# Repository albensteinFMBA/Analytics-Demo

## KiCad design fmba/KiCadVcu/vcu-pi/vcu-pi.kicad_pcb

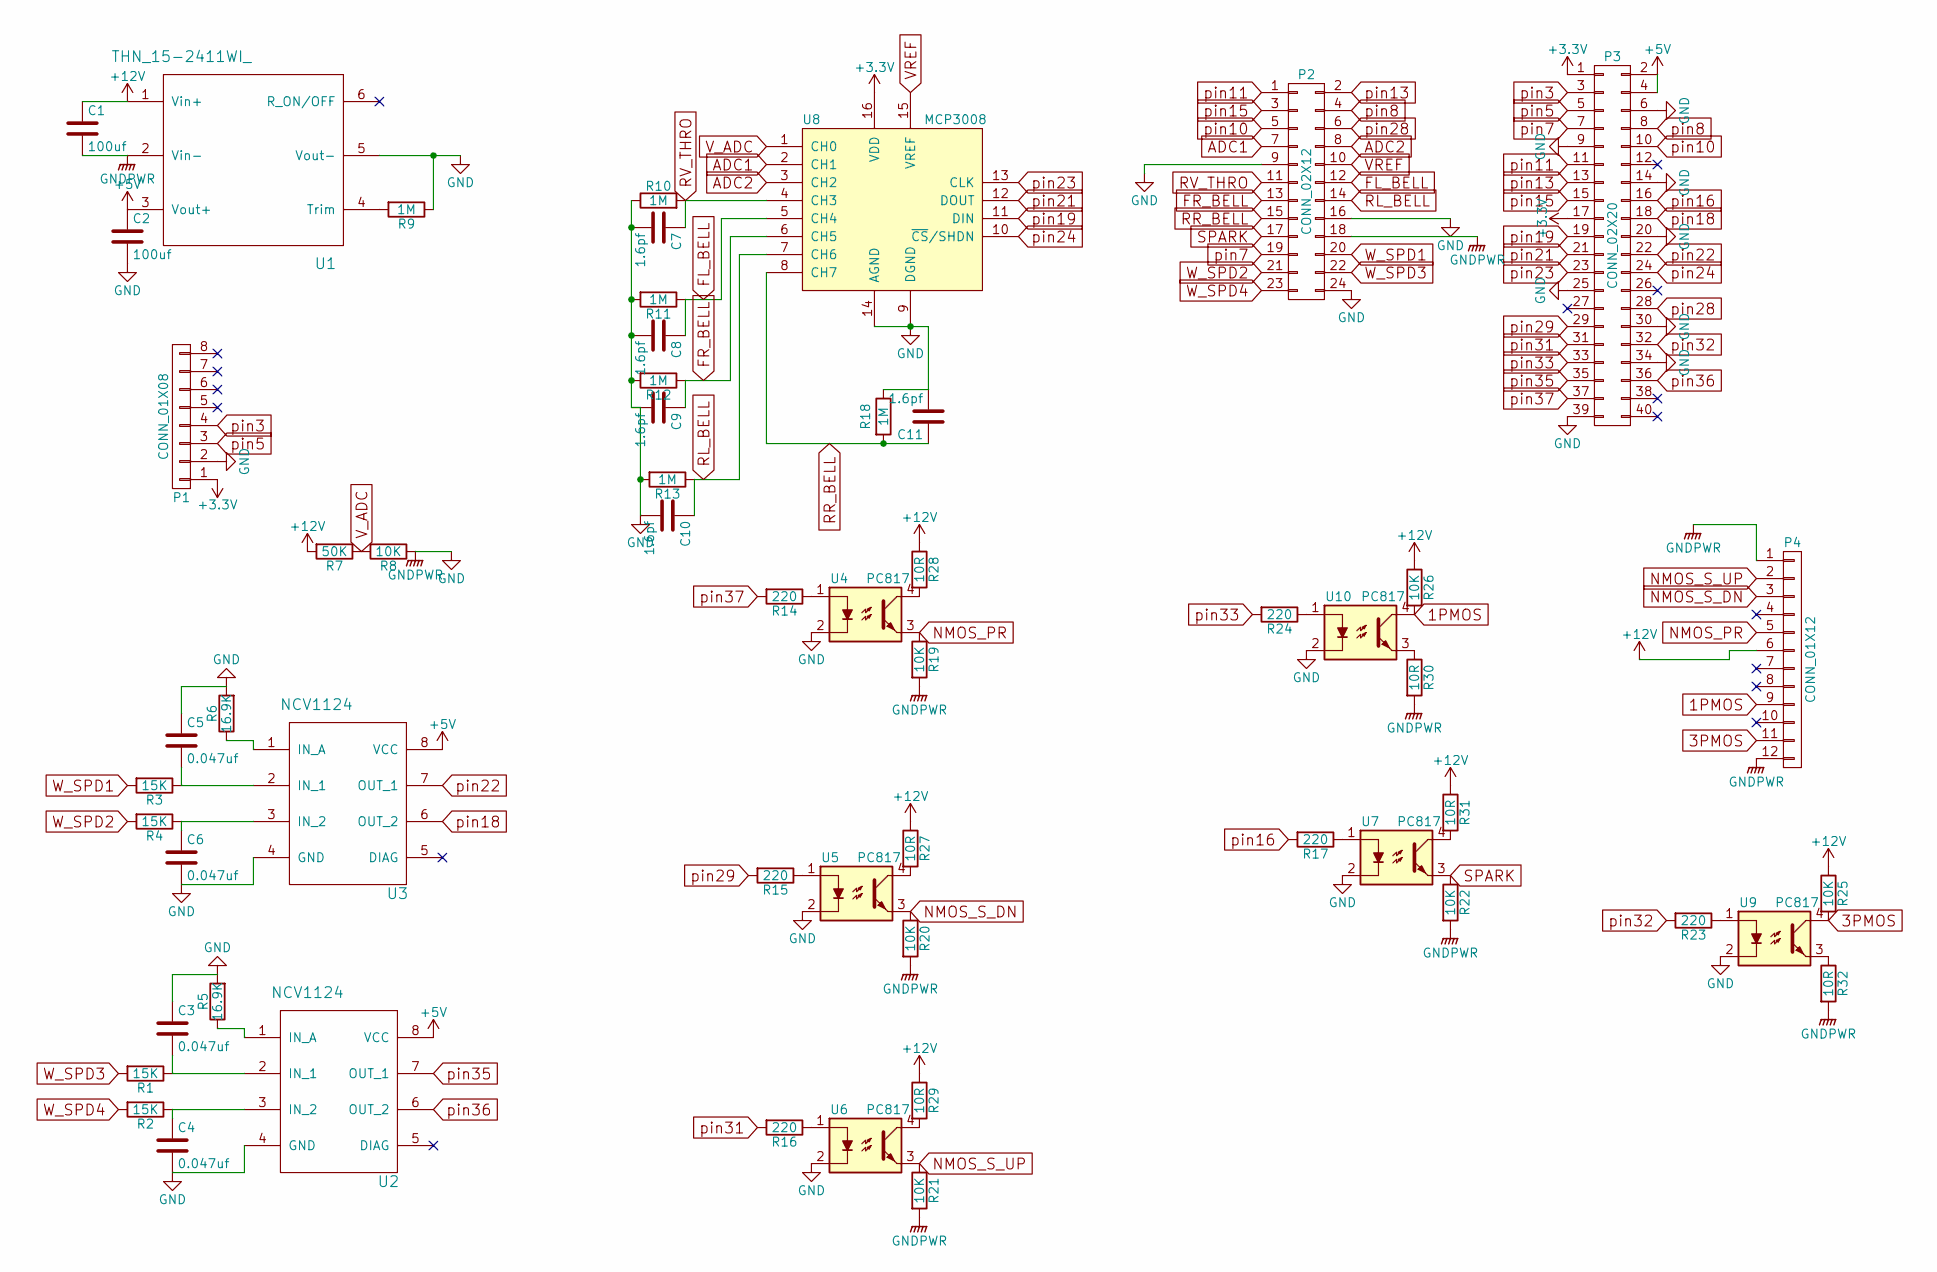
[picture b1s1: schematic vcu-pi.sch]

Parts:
C1, C2: 100uf; C_Radial_D10_L20_P5
C3, C4, C5, C6: 0.047uf; C_Rect_L13_W4_P10
C7, C8, C9, C10, C11: 1.6pf; C_Disc_D3_P2.5
P1: CONN_01X08; Socket_Strip_Straight_1x08
P2: CONN_02X12; connect24_2_12
P3: CONN_02X20; Socket_Strip_Straight_2x20
P4: CONN_01X12; connnector12-1
R1, R2, R3, R4: 15K; Resistor_Horizontal_RM20mm
R5, R6: 16.9K; Resistor_Horizontal_RM7mm
R7: 50K; Resistor_Horizontal_RM10mm
R8: 10K; Resistor_Horizontal_RM10mm
R9, R10, R11, R12, R13, R18: 1M; Resistor_Horizontal_RM10mm
R14, R15, R16, R17, R23, R24: 220; Resistor_Horizontal_RM7mm
R19, R20, R21, R22, R25, R26: 10K; Resistor_Horizontal_RM7mm
R27, R28, R29, R30, R31, R32: 10R; Resistor_Horizontal_RM7mm
U1: THN_15-2411WI_; THN_15-2411WI
U2, U3: NCV1124; SOIC-8_3.9x4.9mm_Pitch1.27mm
U4, U5, U6, U7, U9, U10: PC817; DIP-4_W7.62mm
U8: MCP3008; DIP-16_W7.62mm

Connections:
1PMOS: P4.9, R26.2, U10.4
3PMOS: P4.11, R25.2, U9.4
+3V3: P1.1, P3.1, P3.17, U8.16 (VDD)
+5V: C2.1, P3.2, P3.4, U1.3 (Vout+), U2.8 (VCC), U3.8 (VCC)
+12V: C1.1, P4.6, R7.2, R25.1, R26.1, R27.1, R28.1, R29.1, R31.1, U1.1 (Vin+)
ADC1: P2.7, U8.2 (CH1)
ADC2: P2.8, U8.3 (CH2)
FL_BELL: C8.1, P2.12, R11.1, U8.5 (CH4)
FR_BELL: C9.1, P2.13, R12.1, U8.6 (CH5)
GND: C1.2, C2.2, C3.1, C4.2, C5.1, C6.2, C7.2, C8.2, C9.2, C10.2, C11.2, P1.2, P2.9, P2.16, P2.18, P2.24, P3.6, P3.9, P3.14, P3.20, P3.25, P3.30, P3.34, P3.39, P4.1, P4.12, R5.2, R6.2, R8.1, R9.1, R10.1, R11.2, R12.2, R13.2, R18.1, R19.2, R20.2, R21.2, R22.2, R30.2, R32.2, U1.2 (Vin-), U1.5 (Vout-), U2.4 (GND), U3.4 (GND), U4.2, U5.2, U6.2, U7.2, U8.9 (DGND), U8.14 (AGND), U9.2, U10.2
NMOS_PR: P4.5, R19.1, U4.3
NMOS_S_DN: P4.3, R20.1, U5.3
NMOS_S_UP: P4.2, R21.1, U6.3
unnamed: C3.2, R1.1, U2.2 (IN_1)
unnamed: C4.1, R2.1, U2.3 (IN_2)
unnamed: C5.2, R3.1, U3.2 (IN_1)
unnamed: C6.1, R4.1, U3.3 (IN_2)
unnamed: R5.1, U2.1 (IN_A)
unnamed: R6.1, U3.1 (IN_A)
unnamed: R9.2, U1.4 (Trim)
unnamed: R14.1, U4.1
unnamed: R15.1, U5.1
unnamed: R16.1, U6.1
unnamed: R17.1, U7.1
unnamed: R23.1, U9.1
unnamed: R24.1, U10.1
unnamed: R27.2, U5.4
unnamed: R28.2, U4.4
unnamed: R29.2, U6.4
unnamed: R30.1, U10.3
unnamed: R31.2, U7.4
unnamed: R32.1, U9.3
RL_BELL: C10.1, P2.14, R13.1, U8.7 (CH6)
RR_BELL: C11.1, P2.15, R18.2, U8.8 (CH7)
RV_THRO: C7.1, P2.11, R10.2, U8.4 (CH3)
SPARK: P2.17, R22.1, U7.3
VREF: P2.10, U8.15 (VREF)
V_ADC: R7.1, R8.2, U8.1 (CH0)
W_SPD1: P2.20, R3.2
W_SPD2: P2.21, R4.2
W_SPD3: P2.22, R1.2
W_SPD4: P2.23, R2.2
pin3: P1.4, P3.3
pin5: P1.3, P3.5
pin7: P2.19, P3.7
pin8: P2.4, P3.8
pin10: P2.5, P3.10
pin11: P2.1, P3.11
pin13: P2.2, P3.13
pin15: P2.3, P3.15
pin16: P3.16, R17.2
pin18: P3.18, U3.6 (OUT_2)
pin19: P3.19, U8.11 (DIN)
pin21: P3.21, U8.12 (DOUT)
pin22: P3.22, U3.7 (OUT_1)
pin23: P3.23, U8.13 (CLK)
pin24: P3.24, U8.10 (~CS~/SHDN)
pin28: P2.6, P3.28
pin29: P3.29, R15.2
pin31: P3.31, R16.2
pin32: P3.32, R23.2
pin33: P3.33, R24.2
pin35: P3.35, U2.7 (OUT_1)
pin36: P3.36, U2.6 (OUT_2)
pin37: P3.37, R14.2

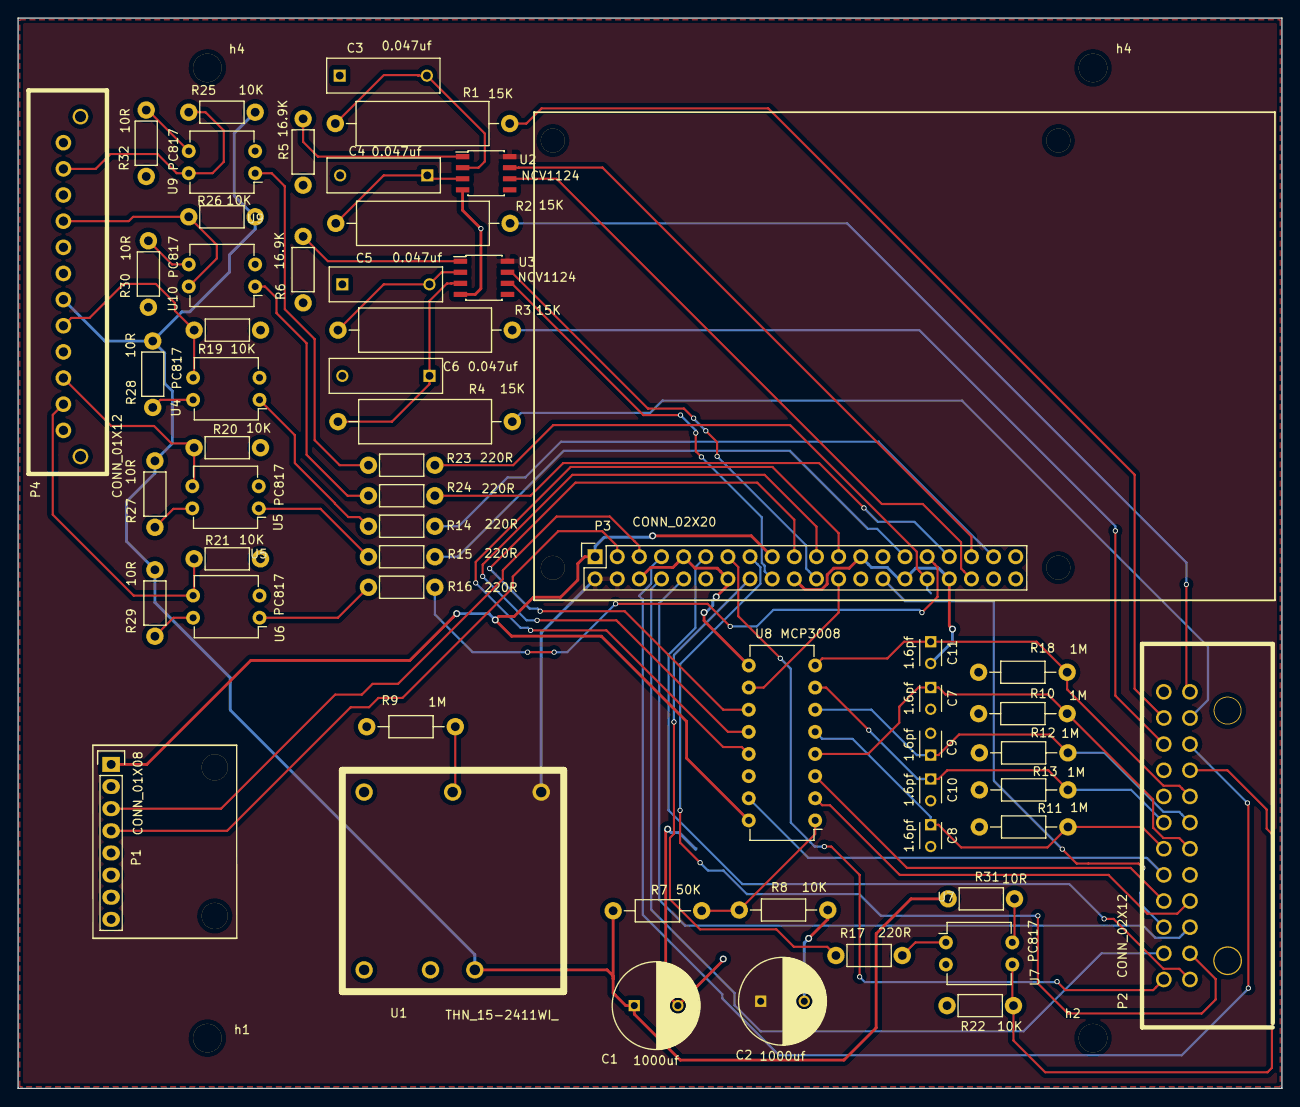
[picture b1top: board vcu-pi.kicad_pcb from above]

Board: 2 copper layers, 145.0 x 122.8 mm, 62 parts (1 on the bottom side), 65 nets.

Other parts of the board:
e: M_HOLE
h1, h2, h4, h4#2: M_HOLE

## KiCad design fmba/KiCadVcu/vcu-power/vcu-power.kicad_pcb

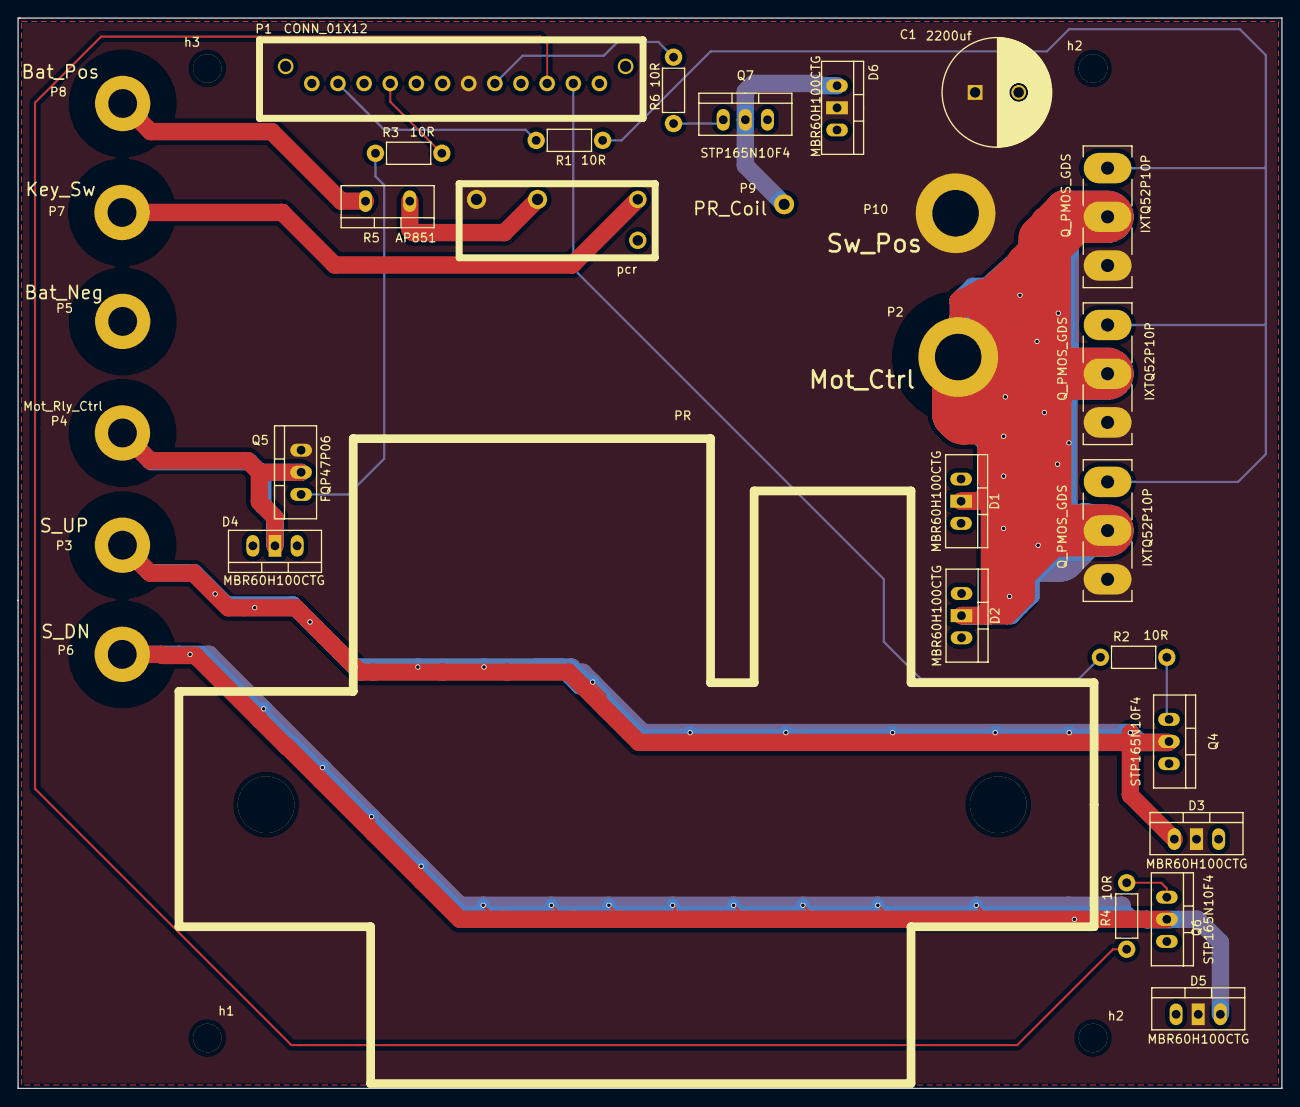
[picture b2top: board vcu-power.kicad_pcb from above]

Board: 2 copper layers, 145.0 x 122.8 mm, 36 parts (1 on the bottom side), 20 nets.

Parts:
C1: 2200uf; C_Radial_D12.5_L25_P5
D1, D2, D3, D4, D5, D6: MBR60H100CTG; Diode_TO-220_Dual_CommonCathode_Vertical
IXTQ52P10P , IXTQ52P10P #2, IXTQ52P10P #3: Q_PMOS_GDS; TO-247_Vertical_Neutral123_largePads
P1: CONN_01X12; connnector12-1
P2: Mot_Ctrl; 0.210''
P3: S_UP; 0.130''
P4: Mot_Rly_Ctrl; 0.130''
P5: Bat_Neg; 0.130''
P6: S_DN; 0.130''
P7: Key_Sw; 0.130''
P8: Bat_Pos; 0.130''
P9: PR_Coil; 0.05''
P10: Sw_Pos; 0.210''
PR: PR
Q4, Q6, Q7: STP165N10F4; TO-220_Neutral123_Vertical
Q5: FQP47P06; TO-220_Neutral123_Vertical
R1, R2, R3, R6: 10R; Resistor_Horizontal_RM7mm
R4: 22; Resistor_Horizontal_RM7mm
R5: AP851; Resistor_TO-220_Vertical
U1: pcr; PCR
h1, h2, h2#2, h3: M_HOLE

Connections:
1PMOS: P1.9, R3.2
3PMOS: IXTQ52P10P.1, IXTQ52P10P #2.1, IXTQ52P10P #3.1, R1.2
+12V: C1.1, D3.2, D5.2, D6.2, IXTQ52P10P.3, IXTQ52P10P #2.3, IXTQ52P10P #3.3, P1.6, P10.1, Q5.3, U1.14
GNDPWR: C1.2, D1.1, D1.3, D2.1, D2.3, D4.1, D4.3, P1.1, P1.12, P5.1, Q4.3, Q6.3, Q7.3, U1.A2
NMOS_PR: P1.5, R6.2
NMOS_S_DN: P1.3, R4.2
NMOS_S_UP: P1.2, R2.2
unnamed: D1.2, D2.2, IXTQ52P10P.2, IXTQ52P10P #2.2, IXTQ52P10P #3.2, P2.1
unnamed: D3.1, P3.1, Q4.2
unnamed: D4.2, P4.1, Q5.2
unnamed: D5.3, P6.1, Q6.2
unnamed: D6.1, P9.1, Q7.2
unnamed: P1.11, R1.1
unnamed: P7.1, U1.A1
unnamed: P8.1, R5.2
unnamed: Q4.1, R2.1
unnamed: Q5.1, R3.1
unnamed: Q6.1, R4.1
unnamed: Q7.1, R6.1
unnamed: R5.1, U1.11

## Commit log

2019-01-04 Create supercross_learner.py
    working with single point contact method. multi-point method results in always "inAir", but bisection portion is working.
2019-01-04 Update supercross_learner.py
    both contact methods are working. the multi-point method results in chatter of the wheel position within the tolerance, and this causes the suspension damper force to go crazy. maybe the suspension d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
2019-01-05 Update supercross_learner.py
    although the model could surely be improved, it appears to be in a state where a more sophisticated track would be nice to test to see if it can jump.
2019-01-07 Create supercross_track_maker.py
    partial work. needs to : make onoff, reverse ski jump, standard and random tracks
2019-01-09 bike jumped for first time
    bike can jump.
    mk_jump is broken for converting to meters
    wheel contacting non-level surfaces seems broken
2019-01-21 Update supercross_track_maker.py
    continued development of smooth track feature creation algorithm
2019-01-22 Update supercross_track_maker.py
    10deg and 30deg mirror jumps working
2019-01-22 Update supercross_track_maker.py
    non-semetrical jumps works too
2019-01-22 Update supercross_track_maker.py
    flat section works
2019-01-22 Update supercross_track_maker.py
    Xdir translation working
2019-01-23 track working. needs cleanup
    adapted mk_<higher level features> functions for new mk_jump.
    added units conversion options, updated learner script
2019-01-23 Update supercross_learner.py
    change debug printing
    explore improvements to bisection, nothing worked.
2019-01-25 bike drives track for first time
    track script had mk_onoff fixed.
    trk2 created
    recrafted physics for better (acceptable) behavior. required time step decrease to 0.001s
    img shows the results for full throttle
2019-01-25 Clean up
    deleted commented out stuff.
2019-01-26 Create supercross_env.py
    create class for environment with openAI Gym style env.step function.
2019-01-27 env class working
    env class working. ready for agent dev.
2019-01-28 partial work for first RL agent
    incomplete work. not tested.
2019-01-29 const throttle sweep done
2019-02-01 working towards configurable approx semi-grad sarsa
    the model runs, but appears to get stuck in first time step. need to debug the env is not stepping.
2019-02-01 add outputs and exe timer, and results of 1st agent
2019-02-05 version2 of agtSarsa
    1] shorten max race time
    2] Normalize all features using learned extremes
    3] Do off policy training using const throttle sims
    4] save bkY, throttle vs X location and theta for each iteration to file.
    5] move action selection to function
2019-02-09 plotting fixed
2019-02-09 ready to run
2019-02-10 first long run
    didn't work.
    rewards are wrong
    also some errors in env: accel force vector direction, decel due to casing wrong
2019-02-10 Update supercross_env.py
    fix reward definition
2019-02-10 Update supercross_track_maker.py
    fix duplicate X coords in mk_trpl
    add grad calc fnc
2019-02-11 second long run. first run after reward fix.
    the env reward was wrong. thas was fixed with hope the learner would learn. this didn't happen. the learner did not behave very differently comapre to when reward was wrong. this is info to suggest t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
2019-02-13 thrid long run. first run after fix of agent execution rate versus env execution rate fix.
    the results look different, but generally, there is no improvement for the linear approx agent.
2019-02-15 forth long run. trk1. first long run with Tabular Q-Learning
2019-02-15 LR005. trk2. second long run with Tabular Q-Learning. didn't work.
2019-04-15 update to formulation of force interaction between wheel and track
    the force interaction was incorrect, this meant penalty for coming up short was inadequate.
    the learner was not updated, but modified for testing the env.
    looks like some other learning run updates squeezed in here as well.
2019-04-24 environment improvements
    1] suspension settings and drop test
2019-04-24 initial commit of FMBA VCU Kicad files
2019-05-08 improve bike model susp and prop
    add accel test track
    update susp calibrations
    add accel test
2019-05-30 kicad rescue changes
2019-05-30 env improvements
    1] significant improvement to track profiles. transition radius are specific to each part of each feature
    2] significant improvement to the realism of the bike acceleration relative to available data
    3] learner updates to support testing of 1 & 2 above
2019-05-30 non-linear suspension
    1] significant improvement to jump realism. suspension travel no longer going negative. bottom out recovery more realistic
2019-05-30 notes aboue variable step solver
2019-06-02 prep for tensorForce
2019-06-04 fixing errors for env to work with TensorForce. step 000
2019-06-05 fixing errors for env to work with TensorForce. step 001
    executed 1 episode successfully.
    something might be wrong with env.reset, since env.mk_state() fails after calling env.reset()
2019-06-07 tensorForce learning is working for mk_trk1
2019-06-09 save worked for checkpont 0
    INFO:tensorflow:Saving checkpoints for 0 into C:\saveTensorForceMoldes\model.ckpt.
2019-06-09 saves every 5sec of realtime
    INFO:tensorflow:Create CheckpointSaverHook.
    INFO:tensorflow:Graph was finalized.
    INFO:tensorflow:Restoring parameters from C:\saveTensorForceMoldes\model.ckpt-0
    INFO:tensorflow:Running local_init_op.
    INFO:tensorflow:Done running local_init_op.
    INFO:tensorflow:Saving checkpoints for 0 into C:\saveTensorForceMoldes\model.ckpt.
2019-06-09 saves every 30 agent<->env steps
    INFO:tensorflow:Create CheckpointSaverHook.
    INFO:tensorflow:Graph was finalized.
    INFO:tensorflow:Restoring parameters from C:\saveTensorForceMoldes\model.ckpt-512
    INFO:tensorflow:Running local_init_op.
    INFO:tensorflow:Done running local_init_op.
    INFO:tensorflow:Saving checkpoints for 512 into C:\saveTensorForceMoldes\model.ckpt.
2019-06-09 saves after every episode
    reloads latest upon restart
    continues episode counting upon restart
2019-06-09 added ideas about track portion of state vector
2019-06-10 sucessfull training restart from saved tf model
    cleaned up and improved the pptx
2019-06-10 saved tf models
2019-06-11 setup for env to run a set of tracks and improved reward
    rewards scaled relative to if race was better than "best for this track" in env
    env now accepts a dict of tracks, and select one at random for each episode
    env tracks best time yet achieved for each "track" in env
2019-06-12 improve performance tracking and plotting for set of tracks
2019-06-14 improve episode number tracking and "end of session" plotting
2019-06-16 improved reporting and saving of env pickle files
    1] better race drawing. only for new best time
    2] env pickle files saved to same dir as TF checkpoints, this ensures each new net restarts with the right data.
    3] updated state to set Xpos past end of track to -1
2019-06-16 adding/removing saved model and env data
    savedTest04 = net04
    savedTest05 = net05
2019-06-16 added net names
2019-06-18 fixing figure saving
2019-06-18 started random track maker function
2019-06-18 updated intro page
2019-06-20 updated links, drop test, track profiles.
2019-06-20 random track working
2019-06-20 updates to support drop test
2019-06-22 updated description of .py files for project and for tensorforce
2019-06-22 created track for on/off
2019-06-22 upate tensorforce .py interaction
2019-07-23 initial working version
    baysian opt of kNN outlier detector
2019-07-24 r precision
    doesn't work, objVal not well defined
2019-07-24 added LOF
    improve objVal definition
2019-08-30 VCU update
2019-08-30 supercross update
2019-08-30 remove auto generated files
